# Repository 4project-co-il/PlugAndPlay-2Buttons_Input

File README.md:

# PlugAndPlay: Input module with 2 buttons
This is the repository with the files for PlugAndPlay input module with 2 buttons

That module has 2 buttons, connected to the 2 interrupt lines and configured to provide interrupt on any change of the button state.

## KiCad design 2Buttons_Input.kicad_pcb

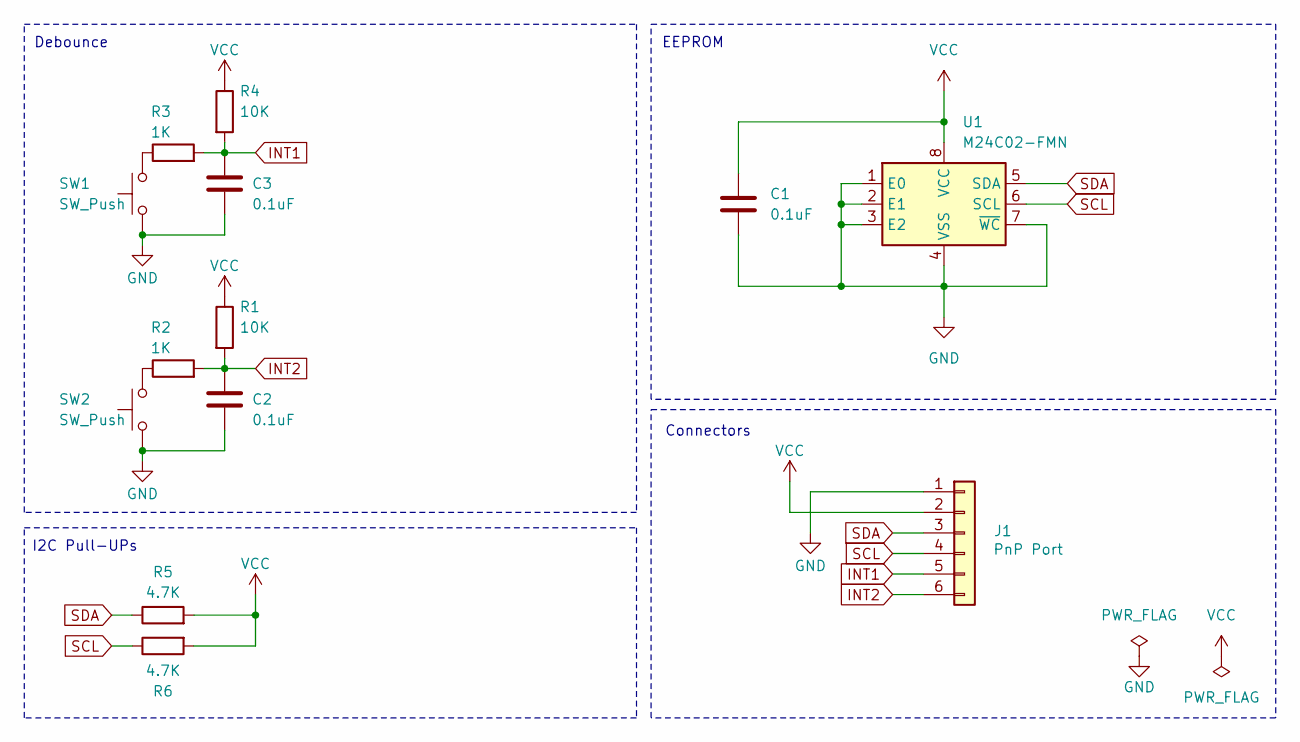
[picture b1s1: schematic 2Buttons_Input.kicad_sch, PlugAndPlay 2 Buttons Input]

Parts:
C1, C2, C3: 0.1uF; C_0603_1608Metric; MPN C14663
J1: JST_SH_SM06B-SRSS-TB_1x06-1MP_P1.00mm_Horizontal; MPN C7430448
R1, R4: 10K; R_0603_1608Metric; MPN C25804
R2, R3: 1K; R_0603_1608Metric; MPN C21190
R5, R6: 4.7K; R_0603_1608Metric; MPN C4190
SW1, SW2: SW_Push; SW_Push_1P1T_NO_CK_PTS125Sx43PSMTR; MPN C19077683
U1: M24C02-FMN; SOIC-8_3.9x4.9mm_P1.27mm; MPN C114502

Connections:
GND: C1.2, C2.2, C3.2, J1.1, SW1.1, SW2.1, U1.1 (E0), U1.2 (E1), U1.3 (E2), U1.4 (VSS), U1.7 (~WC)
INT1: C3.1, J1.5, R3.2, R4.2
INT2: C2.1, J1.6, R1.2, R2.2
unnamed: R2.1, SW2.2
unnamed: R3.1, SW1.2
SCL: J1.4, R6.1, U1.6 (SCL)
SDA: J1.3, R5.1, U1.5 (SDA)
VCC: C1.1, J1.2, R1.1, R4.1, R5.2, R6.2, U1.8 (VCC)

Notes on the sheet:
EEPROM
Connectors
I2C Pull-UPs
Debounce

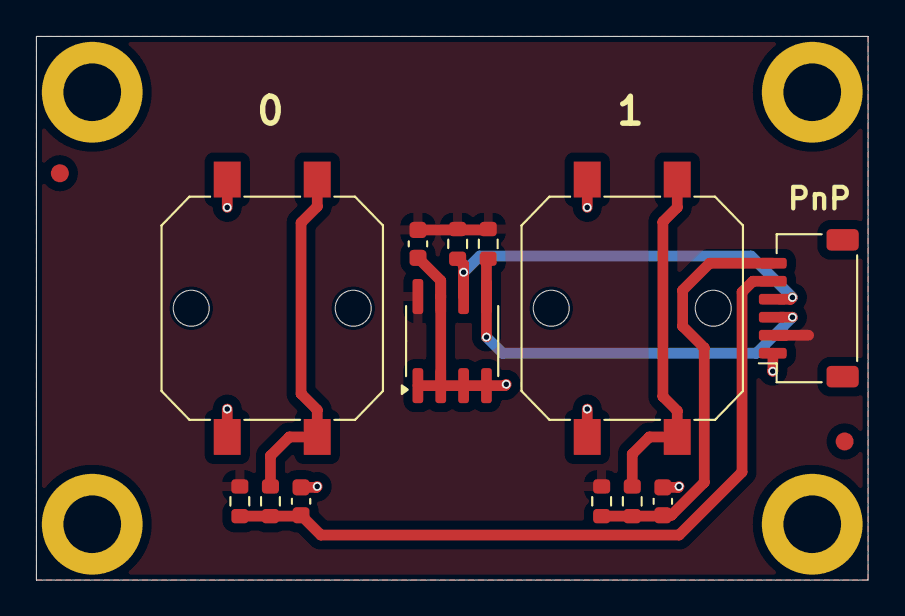
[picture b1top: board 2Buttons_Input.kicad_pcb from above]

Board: 2 copper layers, 46.2 x 30.2 mm, 13 parts (0 on the bottom side), 8 nets.

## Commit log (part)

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2025-05-19 Panel framing on all 4 sides
2025-12-14 Changing the button names on silk level to 0 and 1
